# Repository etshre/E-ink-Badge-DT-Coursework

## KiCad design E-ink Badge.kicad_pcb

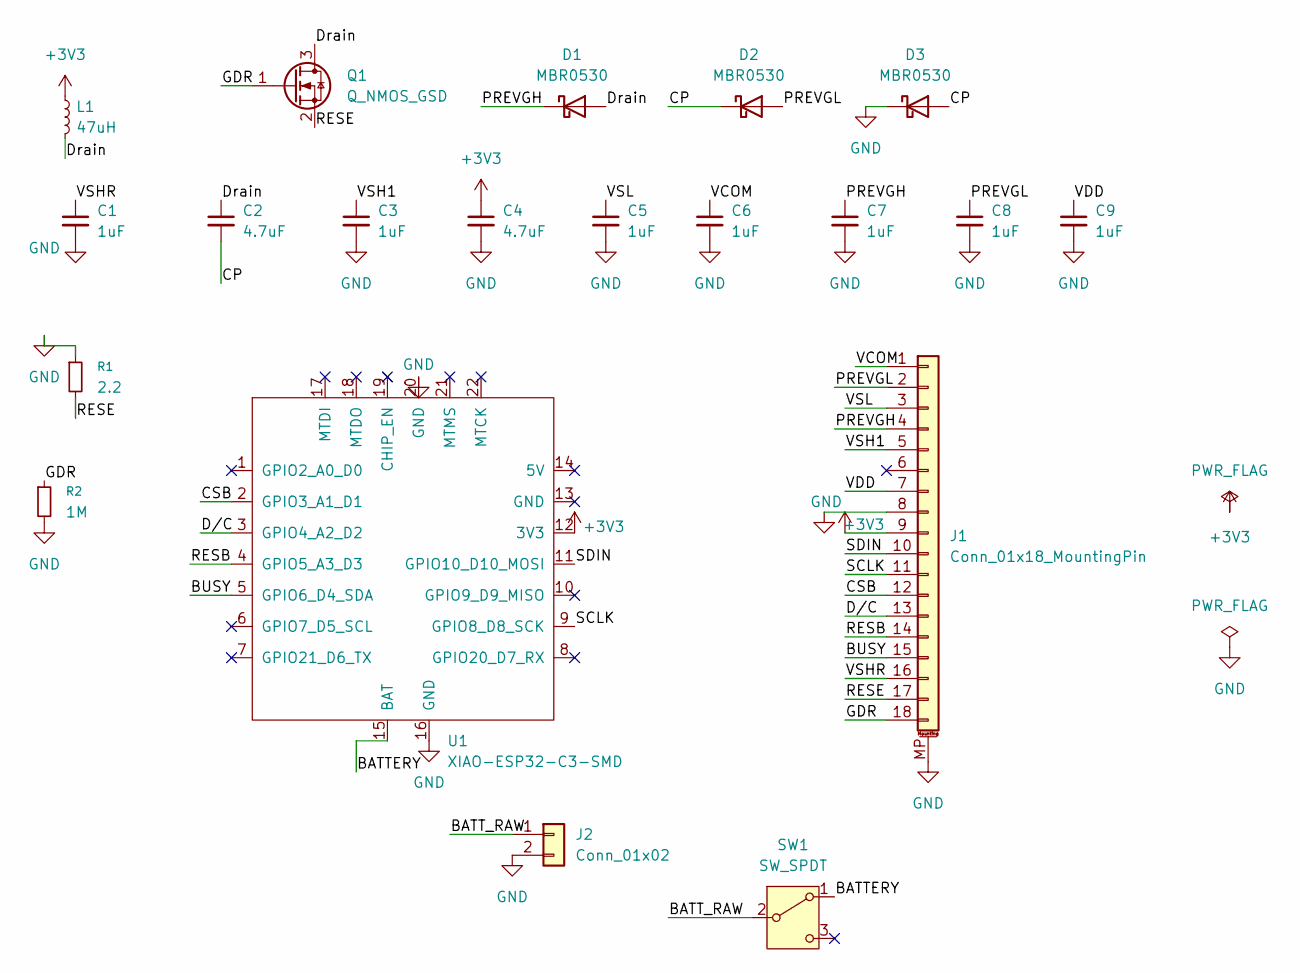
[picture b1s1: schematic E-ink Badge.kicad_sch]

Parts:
C1, C3, C5, C6, C7, C8, C9: 1uF; C_0805_2012Metric_Pad1.18x1.45mm_HandSolder
C2, C4: 4.7uF; C_0805_2012Metric_Pad1.18x1.45mm_HandSolder
D1, D2, D3: MBR0530; D_SOD-123
J1: Conn_01x18_MountingPin; Hirose_FH12-18S-0.5SH_1x18-1MP_P0.50mm_Horizontal
J2: Conn_01x02; JST_PH_S2B-PH-K_1x02_P2.00mm_Horizontal
L1: 47uH; L_Bourns-SRN4018
Q1: Q_NMOS_GSD; SOT-323_SC-70_Handsoldering
R1: 2.2; R_0805_2012Metric_Pad1.20x1.40mm_HandSolder
R2: 1M; R_0805_2012Metric_Pad1.20x1.40mm_HandSolder
SW1: SW_SPDT; SW_SPDT_PCM12
U1: XIAO-ESP32-C3-SMD

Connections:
+3V3: C4.1, J1.9, L1.1, U1.12 (3V3)
/BATTERY: SW1.1 (A), U1.15 (BAT); also elsewhere on the board
/BATT_RAW: J2.1, SW1.2 (B)
/BUSY: J1.15, U1.5 (GPIO6_D4_SDA)
/CP: C2.2, D2.1 (K), D3.2 (A)
/CSB: J1.12, U1.2 (GPIO3_A1_D1)
/Drain: C2.1, D1.2 (A), L1.2, Q1.3 (D)
/D/C: J1.13, U1.3 (GPIO4_A2_D2)
/GDR: J1.18, Q1.1 (G), R2.1
/PREVGH: C7.1, D1.1 (K), J1.4
/PREVGL: C8.1, D2.2 (A), J1.2
/RESB: J1.14, U1.4 (GPIO5_A3_D3)
/RESE: J1.17, Q1.2 (S), R1.2
/SCLK: J1.11, U1.9 (GPIO8_D8_SCK)
/SDIN: J1.10, U1.11 (GPIO10_D10_MOSI)
/VCOM: C6.1, J1.1
/VDD: C9.1, J1.7
/VSH1: C3.1, J1.5
/VSHR: C1.1, J1.16
/VSL: C5.1, J1.3
GND: C1.2, C3.2, C4.2, C5.2, C6.2, C7.2, C8.2, C9.2, D3.1 (K), J1.8, J1.MP (MountPin), J2.2, R1.1, R2.2, U1.16 (GND), U1.20 (GND); also elsewhere on the board

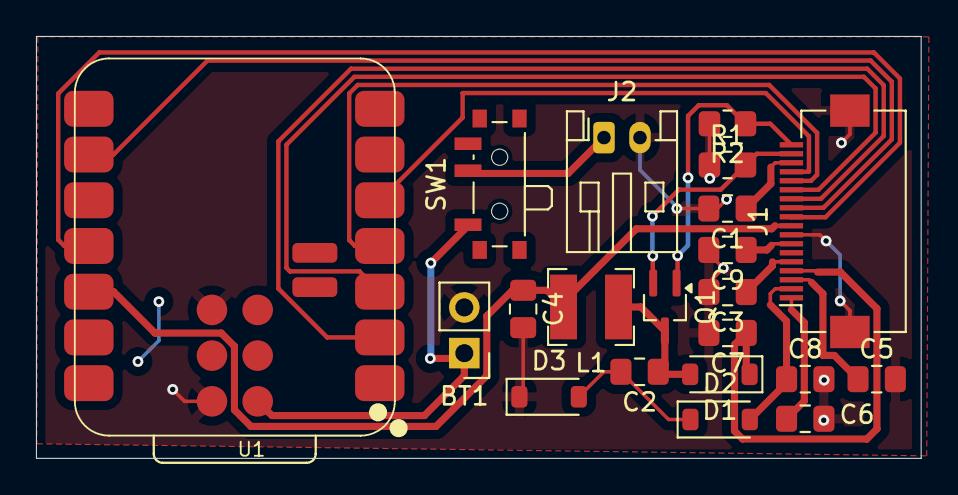
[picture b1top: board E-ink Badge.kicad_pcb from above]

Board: 2 copper layers, 49.2 x 23.4 mm, 21 parts (0 on the bottom side), 21 nets.

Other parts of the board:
BT1: Battery_Cell; PinHeader_1x02_P2.54mm_Vertical

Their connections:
/BATTERY: BT1.1 (+); also elsewhere on the board
GND: BT1.2 (-); also elsewhere on the board
